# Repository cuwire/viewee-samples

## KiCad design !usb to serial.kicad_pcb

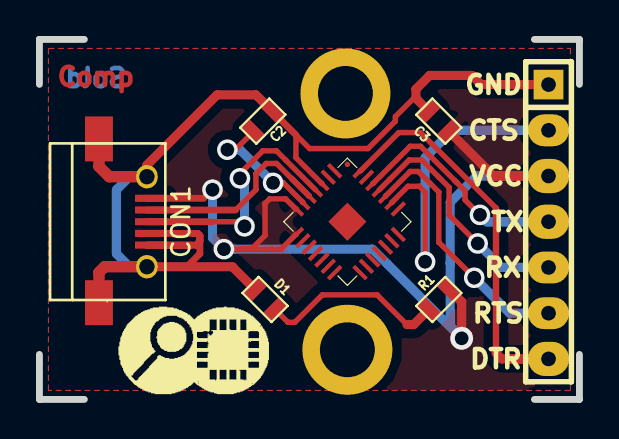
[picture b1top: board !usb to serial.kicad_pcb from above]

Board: 2 copper layers, 30.0 x 20.0 mm, 10 parts (0 on the bottom side), 11 nets.

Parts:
C2: 0.1uF; SM0603
C3: 1uF; SM0603
CON1: USB-MINI-B; USB_Micro-B
D1: LED; SM0603
LOGO: LOGO (2)
P1: CONN_7; SIL-7
P2, P3: CONN_1; 1pin
R1: 330r; SM0603
U1: CP2102; cp2102_xl2

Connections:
/CTS: P1.2, U1.23
/D+: CON1.3, U1.4
/D-: CON1.2, U1.5
/DTR: P1.7, U1.28
/RTS: P1.6, U1.24
/RX: P1.5, U1.25
/TX: P1.4, U1.26
/VCC: C3.1, CON1.1, P1.3, R1.1, U1.7, U1.8
GND: C2.2, C3.2, CON1.4, CON1.5, CON1.6, D1.2, P1.1, U1.3
unnamed: C2.1, U1.6
unnamed: D1.1, R1.2

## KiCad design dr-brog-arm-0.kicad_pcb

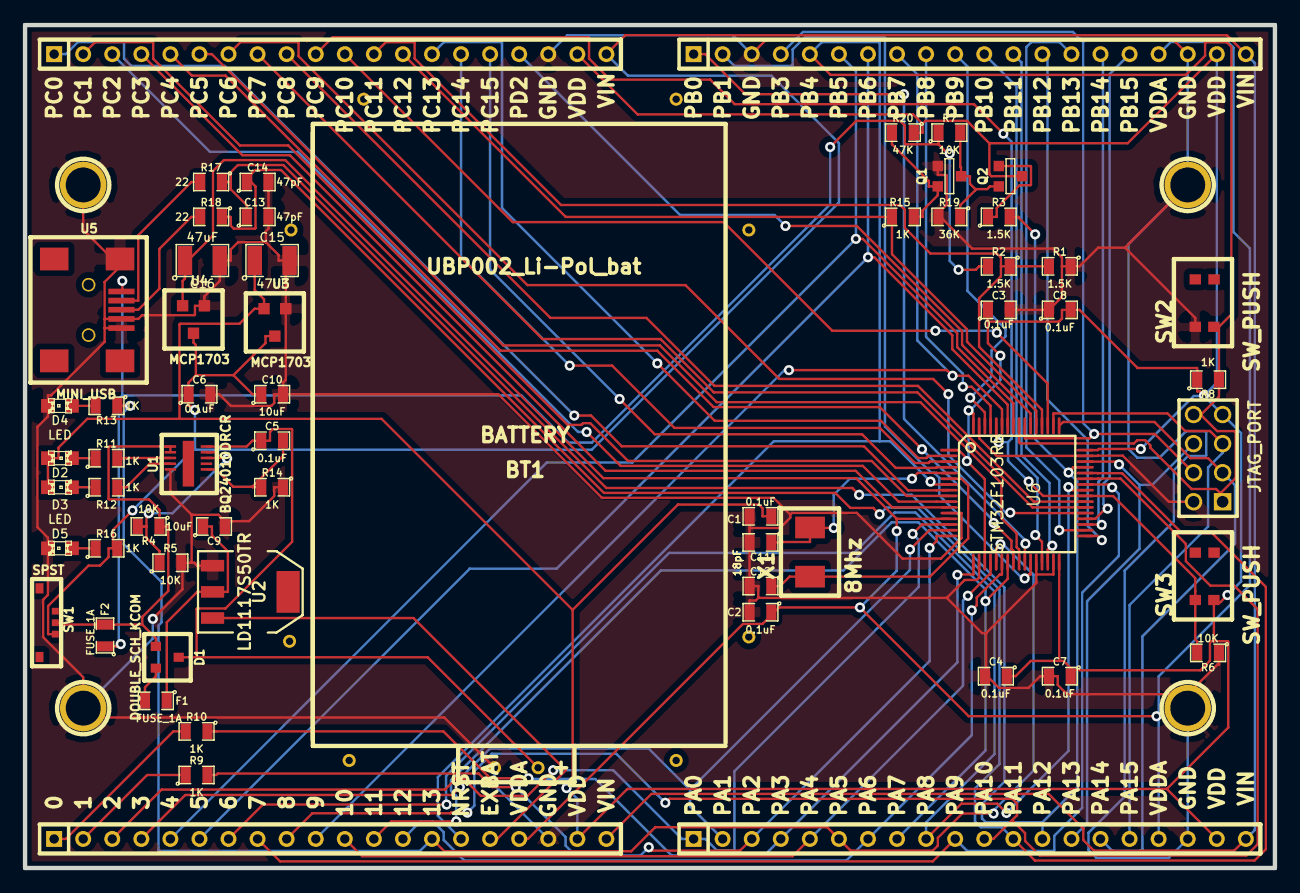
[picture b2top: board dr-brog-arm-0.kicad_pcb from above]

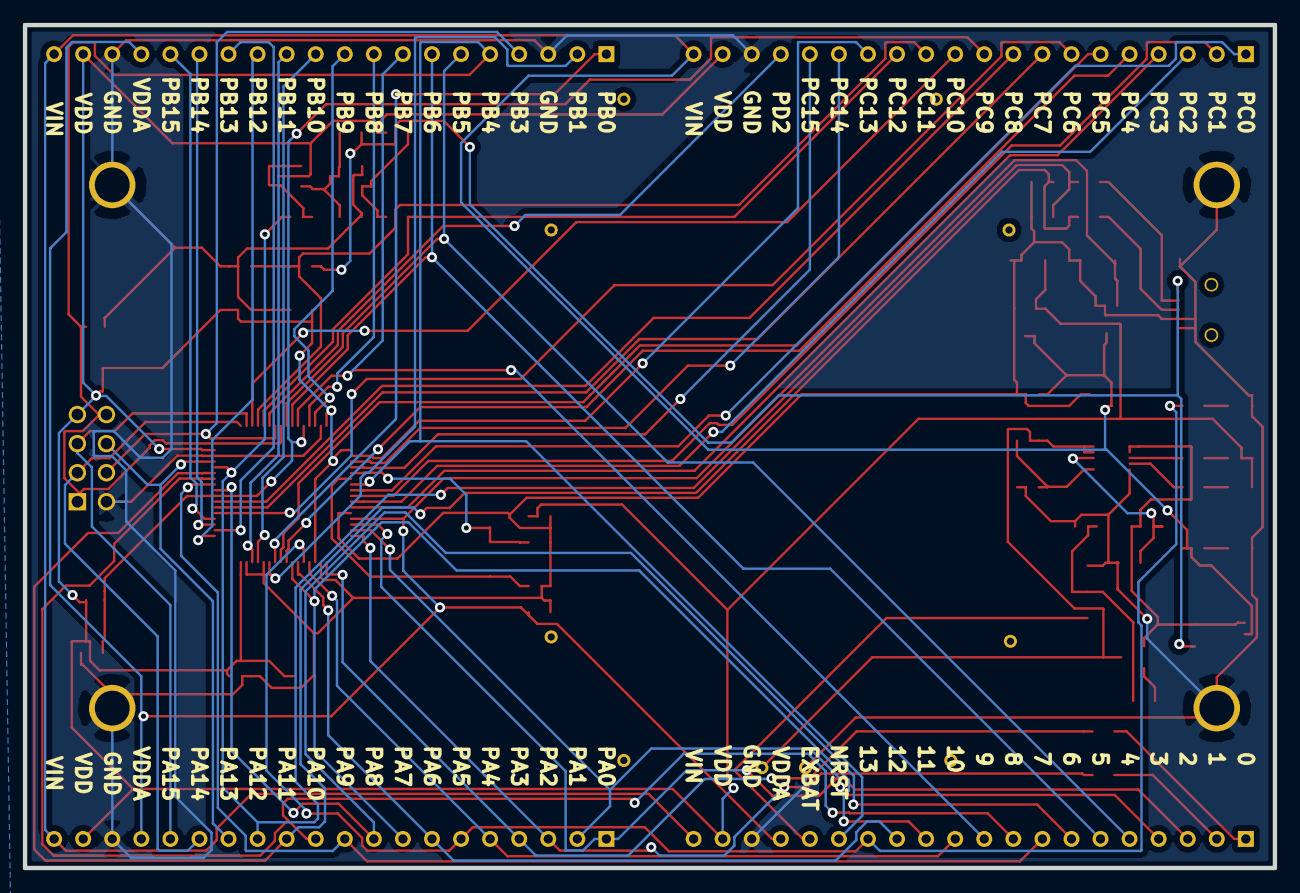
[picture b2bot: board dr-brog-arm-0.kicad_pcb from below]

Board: 2 copper layers, 109.2 x 73.7 mm, 69 parts (4 on the bottom side), 75 nets.

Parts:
BT1: BATTERY; UBP002
C1, C2, C3, C4, C5, C6, C7, C8: 0.1uF; SM0805
C9, C10: 10uF; SM0805
C11, C12: 18pF; SM0805
C13, C14: 47pF; SM0805
C15, C16: 47uF; SM1210
D1: DOUBLE_SCH_KCOM; BAT54C-7-F
D2, D3, D4, D5: LED; LED-0805
F1, F2: FUSE_1A; SM0805
P1, P2, P3, P4: CONN_1; 1pin
P5: CONN_20; PB
P6: CONN_20; PC
P7: CONN_20; PA
P8: CONN_20; PARDUINO
P9: JTAG_PORT; pin_array_4x2
PARDUINO_B_NP: CONN_20; PARDUINO_B_NP
PA_B_NP: CONN_20; PA_B_NP
PB_B_NP: CONN_20; PB_B_NP
PC_B_NP: CONN_20_PC; PC_B_NP
Q1, Q2: BC817K25WE6327XT; SOT23EBC
R1, R2, R3: 1.5K; SM0805
R4, R5, R6, R7: 10K; SM0805
R8, R9, R10, R11, R12, R13, R14, R15, R16: 1K; SM0805
R17, R18: 22; SM0805
R19: 36K; SM0805
R20: 47K; SM0805
SW1: SPST; SSAJ110100
SW2, SW3: SW_PUSH; KMS221GLFS
U1: BQ24010DRCR
U2: LD1117S50TR; SOT223
U3, U4: MCP1703; MCP1703T-3302E
U5: MINI_USB; 154-15320-E
U6: STM32F103RB; TQFP_64
X1: 8Mhz; 815-ABM7-8-D2Y-T

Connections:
+5V: F2.1, R2.2, R7.1, U5.1
+BATT: P8.16, U2.3
/BOOT0: P6.10, R6.2, SW3.1, U6.40, U6.60
/DSBDM: R18.2, U5.3
/J_TDI: P7.16, P9.5, U6.50
/J_TMS: P7.14, P9.6, U6.46
/J_TRS: P5.5, P8.15, P9.1, P9.8, R8.2, SW2.2, U6.7, U6.56
/PA0: P7.1, P8.3, U6.14
/PA1: P7.2, P8.4, U6.15
/PA2: P7.3, R9.2, U6.16
/PA3: P7.4, R10.1, U6.17
/PA4: P7.5, P8.11, U6.20
/PA5: P7.6, P8.14, R13.1, U6.21
/PA6: P7.7, P8.13, U6.22
/PA7: P7.8, P8.12, U6.23
/PA8: P7.9, P8.7, U6.41
/PA9: P7.10, P8.8, U6.42
/PA10: P7.11, P8.9, U6.43
/PA11: C14.1, P7.12, R18.1, U6.44
/PA12: C13.1, P7.13, R3.2, R17.1, U6.45
/PA14: P7.15, P9.3, U6.49
/PB0: P5.1, U6.26
/PB1: P5.2, U6.27
/PB3: P5.4, P9.4, U6.55
/PB5: P5.6, P8.5, U6.57
/PB6: P5.7, P8.6, U6.58
/PB7: P5.8, P8.10, U6.59
/PB8: P5.9, U6.61
/PB9: P5.10, U6.62
/PB10: P5.11, U6.29
/PB11: P5.12, U6.30
/PB12: P5.13, U6.33
/PB13: P5.14, U6.34
/PB14: P5.15, U6.35
/PB15: P5.16, U6.36
/PC0: P6.1, U6.8
/PC1: P6.2, U6.9
/PC2: P6.3, U6.10
/PC3: P6.4, U6.11
/PC4: P6.5, U6.24
/PC5: P6.6, U6.25
/PC6: P6.7, U6.37
/PC7: P6.8, U6.38
/PC8: P6.9, U6.39
/PC10: P6.11, U6.51
/PC11: P6.12, R1.2, R2.1, U6.52
/PC12: P6.13, R15.1, U6.53
/PC13: P6.14, U6.2
/PC14: P6.15, U6.3
/PC15: P6.16, U6.4
/PD0: C11.1, U6.5, X1.1
/PD1: C12.1, U6.6, X1.2
/PD2: P6.17, U6.54
/RX: P8.1, R10.2
/TX: P8.2, R9.1
/USBDP: R17.2, U5.2
/VDD: C1.1, C3.1, C4.1, C7.1, C8.2, C15.1, D2.1, D3.1, P5.19, P6.19, P7.19, P8.19, P9.7, Q2.3, R8.1, R20.1, SW3.2, U3.2, U6.1, U6.19, U6.32, U6.48, U6.64
/VDDA: C2.1, C16.1, P5.17, P7.17, P8.17, U4.2, U6.13
/VIN: C6.1, C10.1, P5.20, P6.20, P7.20, P8.20, R16.2, SW1.2, U3.3, U4.3
GND: BT1.2, C1.2, C2.2, C3.2, C4.2, C6.2, C7.2, C8.1, C9.2, C10.2, C11.2, C12.2, C13.2, C14.2, C15.2, C16.2, D4.2, D5.2, P1.1, P2.1, P3.1, P4.1, P5.3, P5.18, P6.18, P7.18, P8.18, P9.2, Q1.2, R1.1, R5.2, R6.1, R14.1, R19.2, SW2.1, U1.5, U2.1, U3.1, U4.1, U5.4, U5.5, U5.6, U6.12, U6.18, U6.28, U6.31, U6.47, U6.63
unnamed: R4.2, R5.1, U1.8
unnamed: BT1.1, C5.1, D1.3, U1.9, U1.10
unnamed: Q2.2, R3.1
unnamed: D4.1, R13.2
unnamed: D3.2, R12.1
unnamed: R12.2, U1.4
unnamed: R11.2, U1.3
unnamed: D2.2, R11.1
unnamed: Q1.3, Q2.1, R7.2, R19.1
unnamed: D1.1, F1.2
unnamed: C9.1, F1.1, U2.2
unnamed: Q1.1, R15.2, R20.2
unnamed: C5.2, R14.2, U1.6
unnamed: D1.2, F2.2, R4.1, SW1.1, U1.1, U1.2
unnamed: D5.1, R16.1

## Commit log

2017-11-29 initial set of boards to test with viewee.js
